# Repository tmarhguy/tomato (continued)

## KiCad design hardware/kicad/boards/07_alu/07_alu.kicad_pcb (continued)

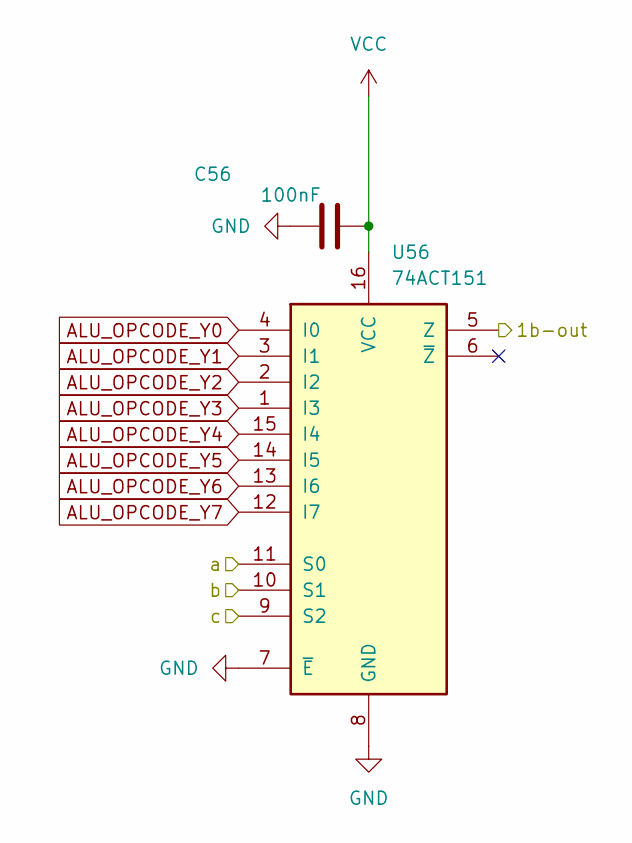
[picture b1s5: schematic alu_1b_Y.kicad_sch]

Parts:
C56: 100nF; C_0603_1608Metric
U56: 74ACT151; SOIC-16_3.9x9.9mm_P1.27mm

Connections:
/alu_4b_1/logB1: U56.5 (Z); also elsewhere on the board
A5: U56.11 (S0); also elsewhere on the board
ALU_OPCODE_Y0: U56.4 (I0); also elsewhere on the board
ALU_OPCODE_Y1: U56.3 (I1); also elsewhere on the board
ALU_OPCODE_Y2: U56.2 (I2); also elsewhere on the board
ALU_OPCODE_Y3: U56.1 (I3); also elsewhere on the board
ALU_OPCODE_Y4: U56.15 (I4); also elsewhere on the board
ALU_OPCODE_Y5: U56.14 (I5); also elsewhere on the board
ALU_OPCODE_Y6: U56.13 (I6); also elsewhere on the board
ALU_OPCODE_Y7: U56.12 (I7); also elsewhere on the board
B5: U56.10 (S1); also elsewhere on the board
C5: U56.9 (S2); also elsewhere on the board
GND: C56.1, U56.7 (~E), U56.8 (GND); also elsewhere on the board
VCC: C56.2, U56.16 (VCC); also elsewhere on the board

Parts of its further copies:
C41, C42, C43, C44, C55, C57, C58: 100nF; C_0603_1608Metric
U41, U42, U43, U44, U53, U54, U55: 74ACT151; SOIC-16_3.9x9.9mm_P1.27mm

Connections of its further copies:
/alu_4b_0/logB0: U41.5 (Z); also elsewhere on the board
/alu_4b_0/logB1: U42.5 (Z); also elsewhere on the board
/alu_4b_0/logB2: U43.5 (Z); also elsewhere on the board
/alu_4b_0/logB3: U44.5 (Z); also elsewhere on the board
/alu_4b_1/logB0: U53.5 (Z); also elsewhere on the board
/alu_4b_1/logB2: U54.5 (Z); also elsewhere on the board
A0: U41.11 (S0); also elsewhere on the board
A1: U42.11 (S0); also elsewhere on the board
A2: U43.11 (S0); also elsewhere on the board
A3: U44.11 (S0); also elsewhere on the board
A4: U53.11 (S0); also elsewhere on the board
A6: U54.11 (S0); also elsewhere on the board
A7: U55.11 (S0); also elsewhere on the board
ALU_OPCODE_Y0: U41.4 (I0), U42.4 (I0), U43.4 (I0), U44.4 (I0), U53.4 (I0), U54.4 (I0), U55.4 (I0); also elsewhere on the board
ALU_OPCODE_Y1: U41.3 (I1), U42.3 (I1), U43.3 (I1), U44.3 (I1), U53.3 (I1), U54.3 (I1), U55.3 (I1); also elsewhere on the board
ALU_OPCODE_Y2: U41.2 (I2), U42.2 (I2), U43.2 (I2), U44.2 (I2), U53.2 (I2), U54.2 (I2), U55.2 (I2); also elsewhere on the board
ALU_OPCODE_Y3: U41.1 (I3), U42.1 (I3), U43.1 (I3), U44.1 (I3), U53.1 (I3), U54.1 (I3), U55.1 (I3); also elsewhere on the board
ALU_OPCODE_Y4: U41.15 (I4), U42.15 (I4), U43.15 (I4), U44.15 (I4), U53.15 (I4), U54.15 (I4), U55.15 (I4); also elsewhere on the board
ALU_OPCODE_Y5: U41.14 (I5), U42.14 (I5), U43.14 (I5), U44.14 (I5), U53.14 (I5), U54.14 (I5), U55.14 (I5); also elsewhere on the board
ALU_OPCODE_Y6: U41.13 (I6), U42.13 (I6), U43.13 (I6), U44.13 (I6), U53.13 (I6), U54.13 (I6), U55.13 (I6); also elsewhere on the board
ALU_OPCODE_Y7: U41.12 (I7), U42.12 (I7), U43.12 (I7), U44.12 (I7), U53.12 (I7), U54.12 (I7), U55.12 (I7); also elsewhere on the board
B0: U41.10 (S1); also elsewhere on the board
B1: U42.10 (S1); also elsewhere on the board
B2: U43.10 (S1); also elsewhere on the board
B3: U44.10 (S1); also elsewhere on the board
B4: U53.10 (S1); also elsewhere on the board
B6: U54.10 (S1); also elsewhere on the board
B7: U55.10 (S1); also elsewhere on the board
Beff: U55.5 (Z); also elsewhere on the board
C0: U41.9 (S2); also elsewhere on the board
C1: U42.9 (S2); also elsewhere on the board
C2: U43.9 (S2); also elsewhere on the board
C3: U44.9 (S2); also elsewhere on the board
C4: U53.9 (S2); also elsewhere on the board
C6: U54.9 (S2); also elsewhere on the board
C7: U55.9 (S2); also elsewhere on the board
GND: C41.1, C42.1, C43.1, C44.1, C55.1, C57.1, C58.1, U41.7 (~E), U41.8 (GND), U42.7 (~E), U42.8 (GND), U43.7 (~E), U43.8 (GND), U44.7 (~E), U44.8 (GND), U53.7 (~E), U53.8 (GND), U54.7 (~E), U54.8 (GND), U55.7 (~E), U55.8 (GND); also elsewhere on the board
VCC: C41.2, C42.2, C43.2, C44.2, C55.2, C57.2, C58.2, U41.16 (VCC), U42.16 (VCC), U43.16 (VCC), U44.16 (VCC), U53.16 (VCC), U54.16 (VCC), U55.16 (VCC); also elsewhere on the board

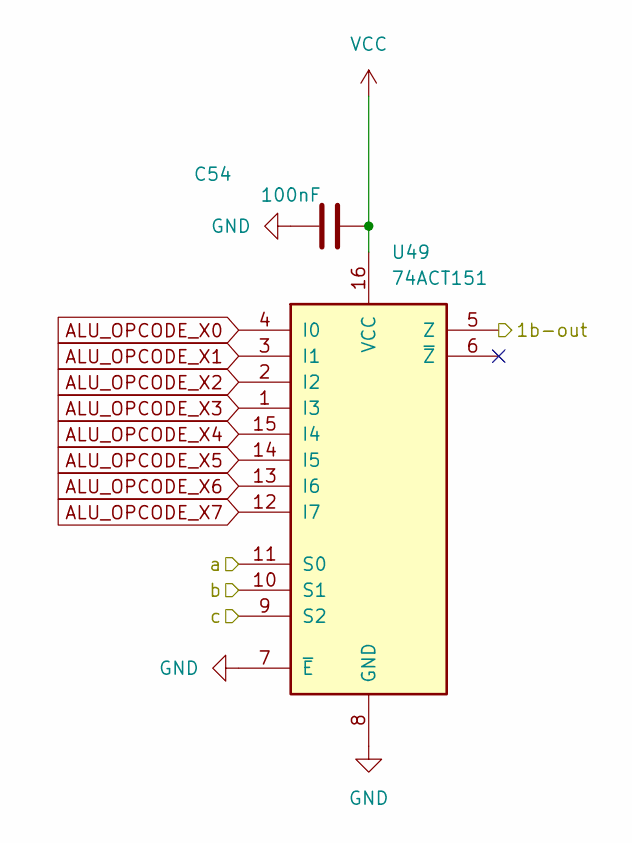
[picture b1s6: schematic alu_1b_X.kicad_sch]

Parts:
C54: 100nF; C_0603_1608Metric
U49: 74ACT151; SOIC-16_3.9x9.9mm_P1.27mm

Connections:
A7: U49.11 (S0); also elsewhere on the board
ALU_OPCODE_X0: U49.4 (I0); also elsewhere on the board
ALU_OPCODE_X1: U49.3 (I1); also elsewhere on the board
ALU_OPCODE_X2: U49.2 (I2); also elsewhere on the board
ALU_OPCODE_X3: U49.1 (I3); also elsewhere on the board
ALU_OPCODE_X4: U49.15 (I4); also elsewhere on the board
ALU_OPCODE_X5: U49.14 (I5); also elsewhere on the board
ALU_OPCODE_X6: U49.13 (I6); also elsewhere on the board
ALU_OPCODE_X7: U49.12 (I7); also elsewhere on the board
Aeff: U49.5 (Z); also elsewhere on the board
B7: U49.10 (S1); also elsewhere on the board
C7: U49.9 (S2); also elsewhere on the board
GND: C54.1, U49.7 (~E), U49.8 (GND); also elsewhere on the board
VCC: C54.2, U49.16 (VCC); also elsewhere on the board

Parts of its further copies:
C45, C46, C47, C48, C51, C52, C53: 100nF; C_0603_1608Metric
U45, U46, U47, U48, U50, U51, U52: 74ACT151; SOIC-16_3.9x9.9mm_P1.27mm

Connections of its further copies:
/alu_4b_0/logA0: U45.5 (Z); also elsewhere on the board
/alu_4b_0/logA1: U46.5 (Z); also elsewhere on the board
/alu_4b_0/logA2: U47.5 (Z); also elsewhere on the board
/alu_4b_0/logA3: U48.5 (Z); also elsewhere on the board
/alu_4b_1/logA0: U50.5 (Z); also elsewhere on the board
/alu_4b_1/logA1: U51.5 (Z); also elsewhere on the board
/alu_4b_1/logA2: U52.5 (Z); also elsewhere on the board
A0: U45.11 (S0); also elsewhere on the board
A1: U46.11 (S0); also elsewhere on the board
A2: U47.11 (S0); also elsewhere on the board
A3: U48.11 (S0); also elsewhere on the board
A4: U50.11 (S0); also elsewhere on the board
A5: U51.11 (S0); also elsewhere on the board
A6: U52.11 (S0); also elsewhere on the board
ALU_OPCODE_X0: U45.4 (I0), U46.4 (I0), U47.4 (I0), U48.4 (I0), U50.4 (I0), U51.4 (I0), U52.4 (I0); also elsewhere on the board
ALU_OPCODE_X1: U45.3 (I1), U46.3 (I1), U47.3 (I1), U48.3 (I1), U50.3 (I1), U51.3 (I1), U52.3 (I1); also elsewhere on the board
ALU_OPCODE_X2: U45.2 (I2), U46.2 (I2), U47.2 (I2), U48.2 (I2), U50.2 (I2), U51.2 (I2), U52.2 (I2); also elsewhere on the board
ALU_OPCODE_X3: U45.1 (I3), U46.1 (I3), U47.1 (I3), U48.1 (I3), U50.1 (I3), U51.1 (I3), U52.1 (I3); also elsewhere on the board
ALU_OPCODE_X4: U45.15 (I4), U46.15 (I4), U47.15 (I4), U48.15 (I4), U50.15 (I4), U51.15 (I4), U52.15 (I4); also elsewhere on the board
ALU_OPCODE_X5: U45.14 (I5), U46.14 (I5), U47.14 (I5), U48.14 (I5), U50.14 (I5), U51.14 (I5), U52.14 (I5); also elsewhere on the board
ALU_OPCODE_X6: U45.13 (I6), U46.13 (I6), U47.13 (I6), U48.13 (I6), U50.13 (I6), U51.13 (I6), U52.13 (I6); also elsewhere on the board
ALU_OPCODE_X7: U45.12 (I7), U46.12 (I7), U47.12 (I7), U48.12 (I7), U50.12 (I7), U51.12 (I7), U52.12 (I7); also elsewhere on the board
B0: U45.10 (S1); also elsewhere on the board
B1: U46.10 (S1); also elsewhere on the board
B2: U47.10 (S1); also elsewhere on the board
B3: U48.10 (S1); also elsewhere on the board
B4: U50.10 (S1); also elsewhere on the board
B5: U51.10 (S1); also elsewhere on the board
B6: U52.10 (S1); also elsewhere on the board
C0: U45.9 (S2); also elsewhere on the board
C1: U46.9 (S2); also elsewhere on the board
C2: U47.9 (S2); also elsewhere on the board
C3: U48.9 (S2); also elsewhere on the board
C4: U50.9 (S2); also elsewhere on the board
C5: U51.9 (S2); also elsewhere on the board
C6: U52.9 (S2); also elsewhere on the board
GND: C45.1, C46.1, C47.1, C48.1, C51.1, C52.1, C53.1, U45.7 (~E), U45.8 (GND), U46.7 (~E), U46.8 (GND), U47.7 (~E), U47.8 (GND), U48.7 (~E), U48.8 (GND), U50.7 (~E), U50.8 (GND), U51.7 (~E), U51.8 (GND), U52.7 (~E), U52.8 (GND); also elsewhere on the board
VCC: C45.2, C46.2, C47.2, C48.2, C51.2, C52.2, C53.2, U45.16 (VCC), U46.16 (VCC), U47.16 (VCC), U48.16 (VCC), U50.16 (VCC), U51.16 (VCC), U52.16 (VCC); also elsewhere on the board

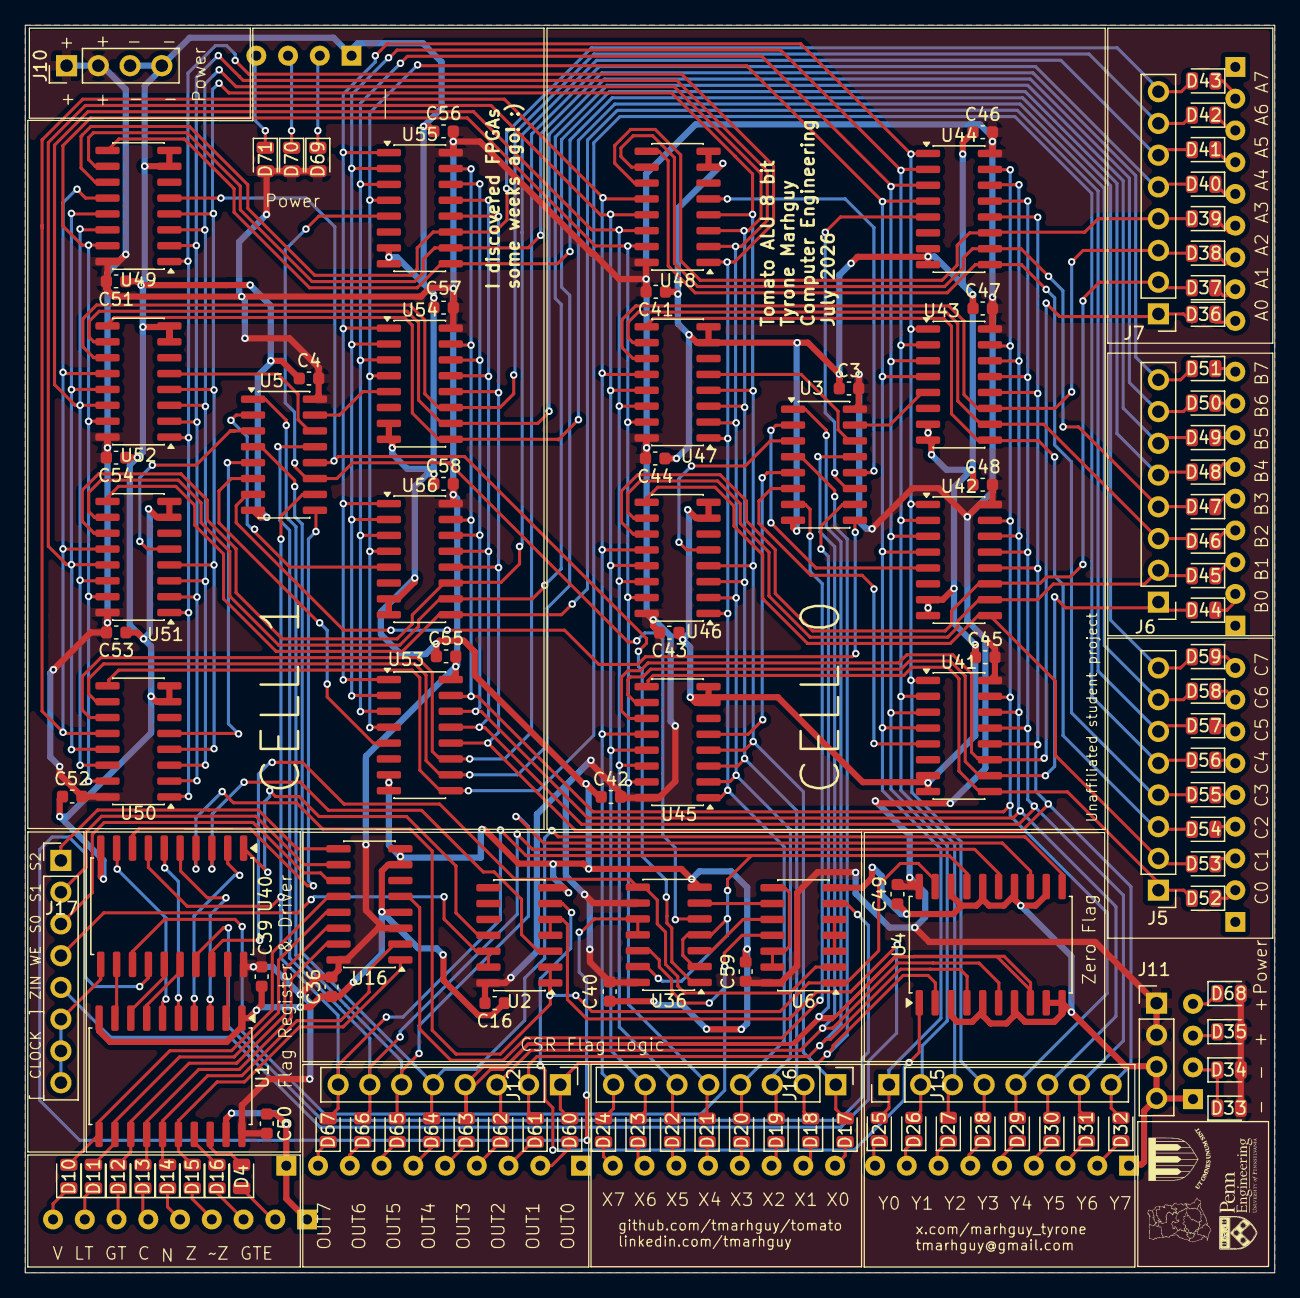
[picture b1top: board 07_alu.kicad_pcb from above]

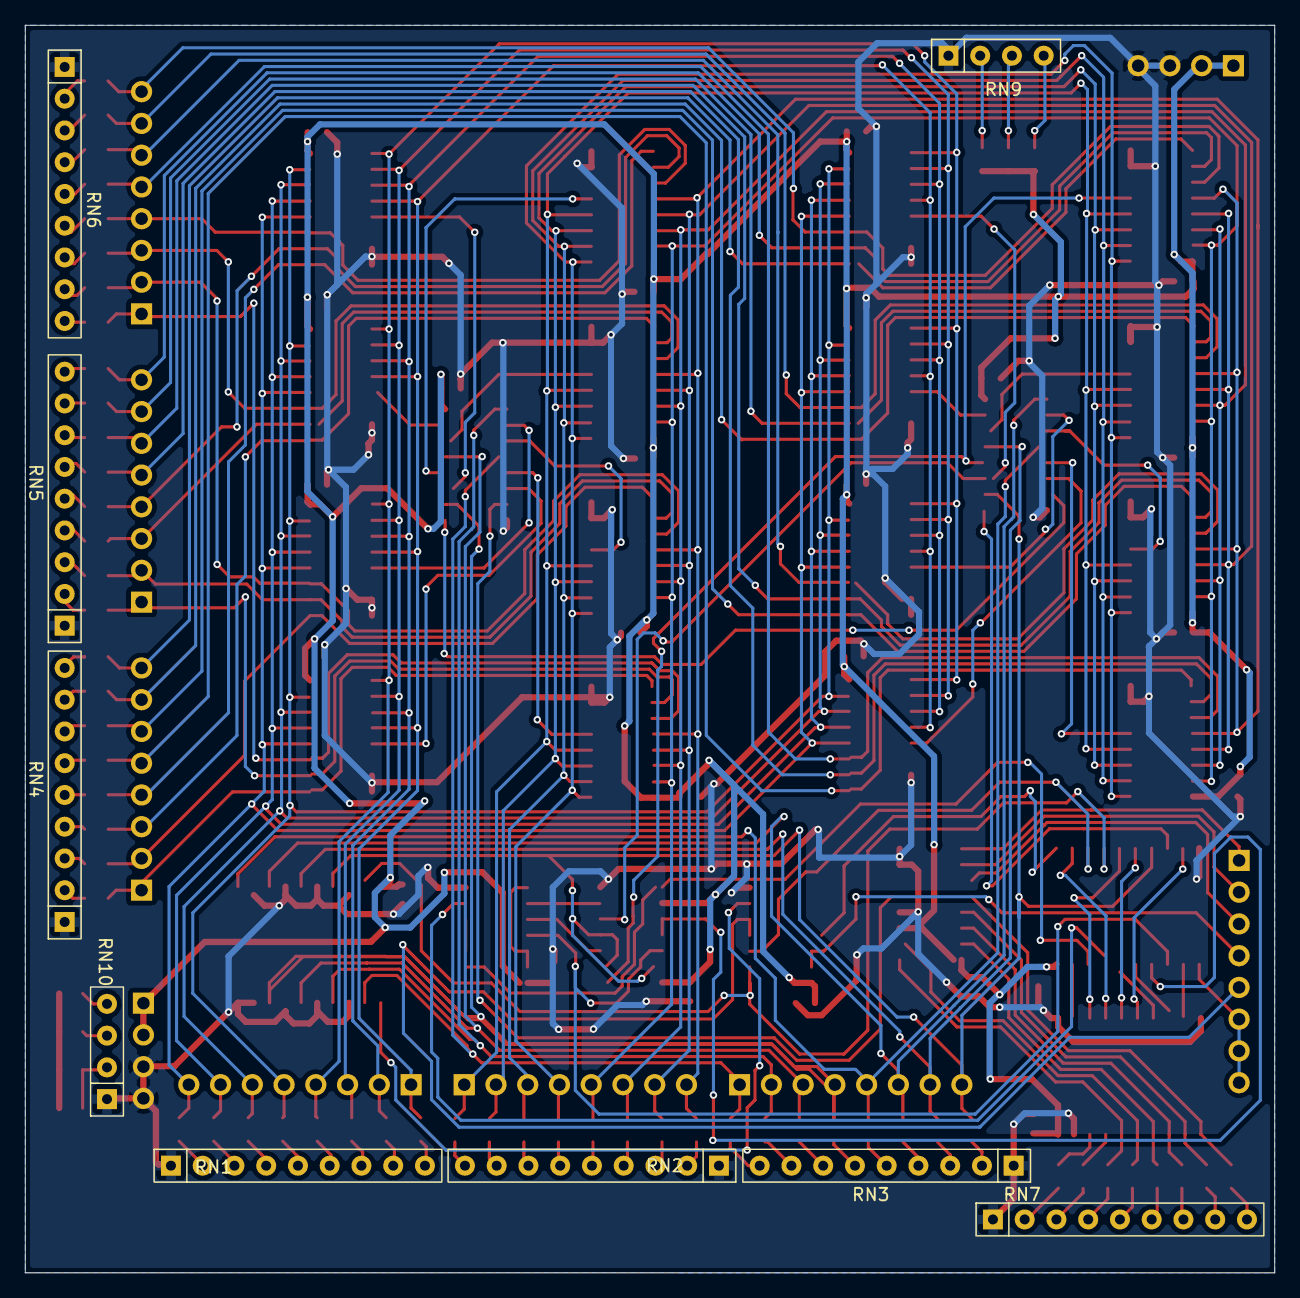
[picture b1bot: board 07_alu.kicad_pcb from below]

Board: 2 copper layers, 100.0 x 99.8 mm, 134 parts (9 on the bottom side), 165 nets.

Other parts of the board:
Ref**: Val**; ghana_map
Ref**#2: Val**; upenn_eng_logo
Ref**#3: Val**; achimota_logo

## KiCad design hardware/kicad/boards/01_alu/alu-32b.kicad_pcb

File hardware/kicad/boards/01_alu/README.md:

# 01 — Early ALU (historical)

<p align="center"><strong>Pre-Tomato experiments · superseded by Lot 07.</strong></p>

Archive lot for early ALU board work. The living Dual-LUT PCB is **[07_alu](../07_alu/README.md)**. The prior 8-bit discrete-transistor story (270×270 mm, ~3,488 devices) is documented at [alu.tmarhguy.com](https://alu.tmarhguy.com).

**Project map:** [Boards](../README.md) · [07_alu](../07_alu/README.md) · [Root README](../../../../README.md)

---

# Legacy notes (transistor-era board)

**Monolithic 8-bit ALU — complete combinational processor on a single PCB** (historical reference below).

## Specifications

| Parameter | Value |
|-----------|-------|
| **Board Size** | 270mm × 270mm (10.6" × 10.6") = **72900 mm²** |
| **Transistor Count** | 3,488 (Hybrid: Discrete + equivalent ICs) → **436 T/bit** |
| **Board mm² / bit** | **≈9112** (72900 / 8) |
| **Architecture** | Pure combinational (no clock) |
| **Layers** | 2 (top signal/power, bottom ground) |
| **Power** | 5V @ 0.5-1A (idle bring-up **&lt;200 mA**) |
| **Propagation Delay** | ~445ns (worst case) |

---

## Functional Blocks

### Arithmetic Unit (Top-Left Quadrant)

**Components:**
- 8× 1-bit full adders (336T)
- 8× XOR gates for B input (96T)
- Carry chain routing

**Function:** A + B or A - B (via 2's complement)

**Signals:**
```
IN:  A[7:0], B[7:0], M
OUT: SUM[7:0], COUT
```

### Logic Unit (Top-Right Quadrant)

**Components:**
- NAND array (32T)
- NOR array (32T)
- XOR array (96T)
- PASS A/B buffers (32T)
- 5:1 MUX (160T)

**Function:** NAND, NOR, XOR, PASS A, PASS B operations

**Signals:**
```
IN:  A[7:0], B[7:0], LOGIC_SEL[2:0]
OUT: LOGIC_OUT[7:0]
```

### Selection & Output (Center)

**Components:**
- 2:1 MUX (160T) - arithmetic vs logic select
- Global inverter (16T)

**Function:** Select result and optionally invert

**Signals:**
```
IN:  ARITH[7:0], LOGIC[7:0], MUX_SEL, INV_OUT
OUT: RESULT[7:0]
```

### Flag Generation (Bottom-Left Quadrant)

**Components:**
- EQUAL comparator (~100T)
- LESS comparator (~120T)
- POSITIVE detector (~20T)

**Function:** Generate comparison and status flags

**Signals:**
```
IN:  A[7:0], B[7:0], OUT[7:0], COUT_IN
OUT: LESS, EQUAL, POSITIVE, COUT
```

### Control Decoder (Bottom-Right Quadrant)

**Components:**
- Combinational decode logic (~68T)

**Function:** FUNC[4:0] → control signals

**Signals:**
```
IN:  FUNC[4:0]
OUT: M, MUX_SEL, INV_OUT, LOGIC_SEL[2:0]
```

---

## Pinout

### Input Pins (22 total)

| Pin Group | Count | Description |
|-----------|-------|-------------|
| A[7:0] | 8 | First operand |
| B[7:0] | 8 | Second operand |
| FUNC[4:0] | 5 | Opcode |
| VCC | 1 | +5V power |
| GND | 1 | Ground (multiple connections) |

### Output Pins (12 total)

| Pin Group | Count | Description |
|-----------|-------|-------------|
| OUT[7:0] | 8 | Result |
| LESS | 1 | Less than flag |
| EQUAL | 1 | Equal flag |
| POSITIVE | 1 | Positive flag |
| COUT | 1 | Carry out flag |

---

## Fabrication

### Manufacturing Requirements

**PCB Specs:**
- **Size:** 270×270mm (**confirm manufacturer supports large format**)
- **Layers:** 2
- **Thickness:** 1.6mm
- **Copper:** 1oz (35µm)
- **Min trace/space:** 0.2mm/0.2mm
- **Surface finish:** HASL lead-free

### Assembly

**Component count:**
- 3,488 transistors (624 Discrete + 2,864 in ICs + Support)
- ~500 resistors (10kΩ pull-ups, 220Ω current limiting)
- ~50 capacitors (100nF decoupling)
- 36x 74HC157 + 10x 74HC86 ICs
- Headers, test points

**Estimated assembly time:** 50-70 hours (hand soldering)

---

## Testing

### Power-On Test

```
1. Visual inspection
2. Continuity: VCC, GND
3. Resistance: VCC-GND > 10kΩ
4. Power-on: Measure current < 200mA idle
5. Voltage: VCC = 5.0V ± 0.1V at all points
```

### Functional Test

```
Test ADD operation:
  FUNC = 00000
  A = 0x01
  B = 0x01
  Expected OUT = 0x02
  Measure with multimeter or logic analyzer
```

---

## References

- [Schematic](main_alu.kicad_sch) - Complete circuit
- [PCB Layout](main_alu.kicad_pcb) - Board layout
- [Architecture](../../../docs/ARCHITECTURE.md) - System design

---

**Status:** Design complete, fabrication-ready  
**Last Updated:** 2026-01-16

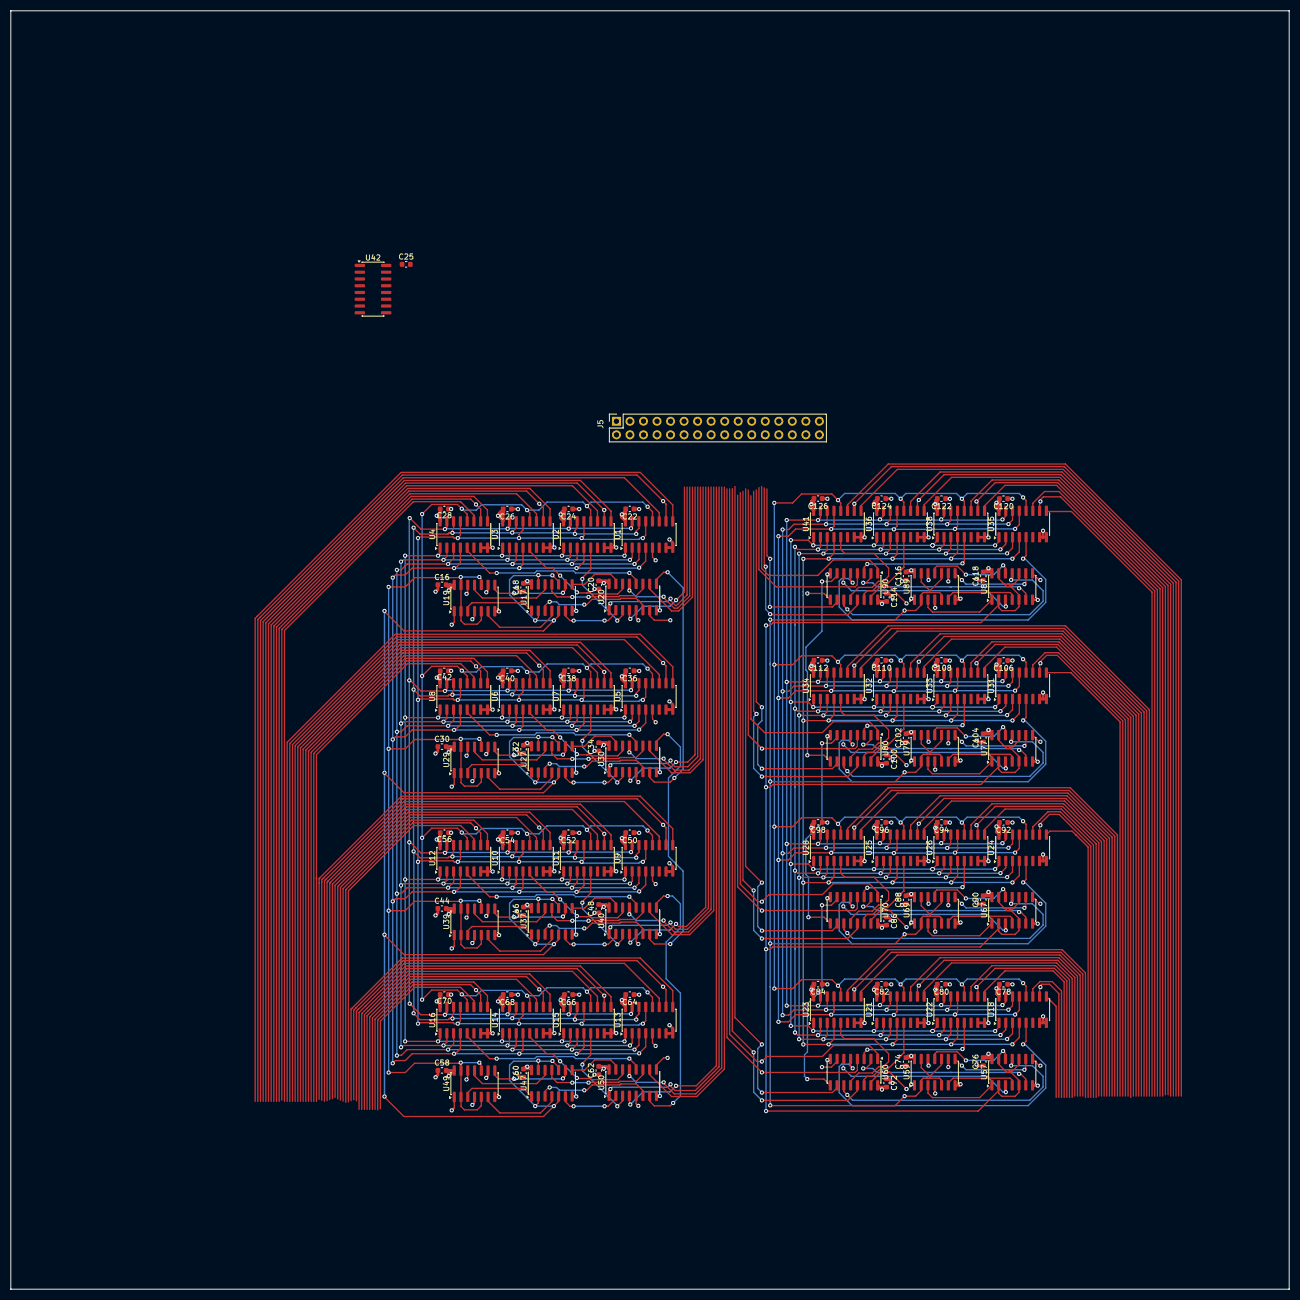
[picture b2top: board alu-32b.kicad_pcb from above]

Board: 4 copper layers, 240.0 x 240.0 mm, 115 parts (0 on the bottom side), 179 nets.

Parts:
C16, C18, C20, C22, C24, C25, C26, C28, C30, C32, C34, C36, C38, C40, C42, C44, C46, C48, C50, C52, C54, C56, C58, C60, C62, C64, C66, C68, C70, C72, C74, C76, C78, C80, C82, C84, C86, C88, C90, C92, C94, C96, C98, C100, C102, C104, C106, C108, C110, C112, C114, C116, C118, C120, C122, C124, C126: 100nF; C_0603_1608Metric
J5: Conn_02x16_Counter_Clockwise; PinSocket_2x16_P2.54mm_Vertical
U1, U2, U3, U4, U5, U6, U7, U8, U9, U10, U11, U12, U13, U14, U15, U16, U18, U21, U22, U23, U24, U25, U26, U28, U31, U32, U33, U34, U35, U36, U38, U41, U42: 74ACT151; SOIC-16_3.9x9.9mm_P1.27mm
U17, U27, U37, U47, U57, U67, U77, U87: 74HC86; SOIC-14_3.9x8.7mm_P1.27mm
U19, U29, U39, U49, U59, U69, U79, U89: 74HC00; SOIC-14_3.9x8.7mm_P1.27mm
U20, U30, U40, U50, U60, U70, U80, U90: 74ACT283; SOIC-16_3.9x9.9mm_P1.27mm

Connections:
/alu-4b-0/log0: U1.5 (Z), U20.5 (A1)
/alu-4b-0/log1: U2.5 (Z), U20.3 (A2)
/alu-4b-0/log2: U3.5 (Z), U20.14 (A3)
/alu-4b-0/log3: U4.5 (Z), U20.12 (A4)
/alu-4b-0/sB0: U17.3, U20.6 (B1)
/alu-4b-0/sB1: U17.6, U20.2 (B2)
/alu-4b-0/sB2: U17.8, U20.15 (B3)
/alu-4b-0/sB3: U17.11, U20.11 (B4)
/alu-4b-1/log0: U5.5 (Z), U30.5 (A1)
/alu-4b-1/log1: U7.5 (Z), U30.3 (A2)
/alu-4b-1/log2: U6.5 (Z), U30.14 (A3)
/alu-4b-1/log3: U8.5 (Z), U30.12 (A4)
/alu-4b-1/sB0: U27.3, U30.6 (B1)
/alu-4b-1/sB1: U27.6, U30.2 (B2)
/alu-4b-1/sB2: U27.8, U30.15 (B3)
/alu-4b-1/sB3: U27.11, U30.11 (B4)
/alu-4b-2/log0: U9.5 (Z), U40.5 (A1)
/alu-4b-2/log1: U11.5 (Z), U40.3 (A2)
/alu-4b-2/log2: U10.5 (Z), U40.14 (A3)
/alu-4b-2/log3: U12.5 (Z), U40.12 (A4)
/alu-4b-2/sB0: U37.3, U40.6 (B1)
/alu-4b-2/sB1: U37.6, U40.2 (B2)
/alu-4b-2/sB2: U37.8, U40.15 (B3)
/alu-4b-2/sB3: U37.11, U40.11 (B4)
/alu-4b-3/log0: U13.5 (Z), U50.5 (A1)
/alu-4b-3/log1: U15.5 (Z), U50.3 (A2)
/alu-4b-3/log2: U14.5 (Z), U50.14 (A3)
/alu-4b-3/log3: U16.5 (Z), U50.12 (A4)
/alu-4b-3/sB0: U47.3, U50.6 (B1)
/alu-4b-3/sB1: U47.6, U50.2 (B2)
/alu-4b-3/sB2: U47.8, U50.15 (B3)
/alu-4b-3/sB3: U47.11, U50.11 (B4)
/alu-4b-4/log0: U18.5 (Z), U60.5 (A1)
/alu-4b-4/log1: U22.5 (Z), U60.3 (A2)
/alu-4b-4/log2: U21.5 (Z), U60.14 (A3)
/alu-4b-4/log3: U23.5 (Z), U60.12 (A4)
/alu-4b-4/sB0: U57.3, U60.6 (B1)
/alu-4b-4/sB1: U57.6, U60.2 (B2)
/alu-4b-4/sB2: U57.8, U60.15 (B3)
/alu-4b-4/sB3: U57.11, U60.11 (B4)
/alu-4b-5/log0: U24.5 (Z), U70.5 (A1)
/alu-4b-5/log1: U26.5 (Z), U70.3 (A2)
/alu-4b-5/log2: U25.5 (Z), U70.14 (A3)
/alu-4b-5/log3: U28.5 (Z), U70.12 (A4)
/alu-4b-5/sB0: U67.3, U70.6 (B1)
/alu-4b-5/sB1: U67.6, U70.2 (B2)
/alu-4b-5/sB2: U67.8, U70.15 (B3)
/alu-4b-5/sB3: U67.11, U70.11 (B4)
/alu-4b-6/log0: U31.5 (Z), U80.5 (A1)
/alu-4b-6/log1: U33.5 (Z), U80.3 (A2)
/alu-4b-6/log2: U32.5 (Z), U80.14 (A3)
/alu-4b-6/log3: U34.5 (Z), U80.12 (A4)
/alu-4b-6/sB0: U77.3, U80.6 (B1)
/alu-4b-6/sB1: U77.6, U80.2 (B2)
/alu-4b-6/sB2: U77.8, U80.15 (B3)
/alu-4b-6/sB3: U77.11, U80.11 (B4)
/alu-4b-7/log0: U35.5 (Z), U90.5 (A1)
/alu-4b-7/log1: U38.5 (Z), U90.3 (A2)
/alu-4b-7/log2: U36.5 (Z), U90.14 (A3)
/alu-4b-7/sB0: U87.3, U90.6 (B1)
/alu-4b-7/sB1: U87.6, U90.2 (B2)
/alu-4b-7/sB2: U87.8, U90.15 (B3)
/cout0: U20.9 (C4), U30.7 (C0)
/cout1: U30.9 (C4), U40.7 (C0)
/cout2: U40.9 (C4), U50.7 (C0)
/cout3: U50.9 (C4), U60.7 (C0)
/cout4: U60.9 (C4), U70.7 (C0)
/cout5: U70.9 (C4), U80.7 (C0)
/cout6: U80.9 (C4), U90.7 (C0)
AEFF31: U41.5 (Z), U90.12 (A4)
ALU-OPCODE0: U1.4 (I0), U2.4 (I0), U3.4 (I0), U4.4 (I0), U5.4 (I0), U6.4 (I0), U7.4 (I0), U8.4 (I0), U9.4 (I0), U10.4 (I0), U11.4 (I0), U12.4 (I0), U13.4 (I0), U14.4 (I0), U15.4 (I0), U16.4 (I0), U18.4 (I0), U21.4 (I0), U22.4 (I0), U23.4 (I0), U24.4 (I0), U25.4 (I0), U26.4 (I0), U28.4 (I0), U31.4 (I0), U32.4 (I0), U33.4 (I0), U34.4 (I0), U35.4 (I0), U36.4 (I0), U38.4 (I0), U41.4 (I0)
ALU-OPCODE1: U1.3 (I1), U2.3 (I1), U3.3 (I1), U4.3 (I1), U5.3 (I1), U6.3 (I1), U7.3 (I1), U8.3 (I1), U9.3 (I1), U10.3 (I1), U11.3 (I1), U12.3 (I1), U13.3 (I1), U14.3 (I1), U15.3 (I1), U16.3 (I1), U18.3 (I1), U21.3 (I1), U22.3 (I1), U23.3 (I1), U24.3 (I1), U25.3 (I1), U26.3 (I1), U28.3 (I1), U31.3 (I1), U32.3 (I1), U33.3 (I1), U34.3 (I1), U35.3 (I1), U36.3 (I1), U38.3 (I1), U41.3 (I1)
ALU-OPCODE2: U1.2 (I2), U2.2 (I2), U3.2 (I2), U4.2 (I2), U5.2 (I2), U6.2 (I2), U7.2 (I2), U8.2 (I2), U9.2 (I2), U10.2 (I2), U11.2 (I2), U12.2 (I2), U13.2 (I2), U14.2 (I2), U15.2 (I2), U16.2 (I2), U18.2 (I2), U21.2 (I2), U22.2 (I2), U23.2 (I2), U24.2 (I2), U25.2 (I2), U26.2 (I2), U28.2 (I2), U31.2 (I2), U32.2 (I2), U33.2 (I2), U34.2 (I2), U35.2 (I2), U36.2 (I2), U38.2 (I2), U41.2 (I2)
ALU-OPCODE3: U1.1 (I3), U2.1 (I3), U3.1 (I3), U4.1 (I3), U5.1 (I3), U6.1 (I3), U7.1 (I3), U8.1 (I3), U9.1 (I3), U10.1 (I3), U11.1 (I3), U12.1 (I3), U13.1 (I3), U14.1 (I3), U15.1 (I3), U16.1 (I3), U18.1 (I3), U21.1 (I3), U22.1 (I3), U23.1 (I3), U24.1 (I3), U25.1 (I3), U26.1 (I3), U28.1 (I3), U31.1 (I3), U32.1 (I3), U33.1 (I3), U34.1 (I3), U35.1 (I3), U36.1 (I3), U38.1 (I3), U41.1 (I3)
ALU-OPCODE4: U1.15 (I4), U2.15 (I4), U3.15 (I4), U4.15 (I4), U5.15 (I4), U6.15 (I4), U7.15 (I4), U8.15 (I4), U9.15 (I4), U10.15 (I4), U11.15 (I4), U12.15 (I4), U13.15 (I4), U14.15 (I4), U15.15 (I4), U16.15 (I4), U18.15 (I4), U21.15 (I4), U22.15 (I4), U23.15 (I4), U24.15 (I4), U25.15 (I4), U26.15 (I4), U28.15 (I4), U31.15 (I4), U32.15 (I4), U33.15 (I4), U34.15 (I4), U35.15 (I4), U36.15 (I4), U38.15 (I4), U41.15 (I4)
ALU-OPCODE5: U1.14 (I5), U2.14 (I5), U3.14 (I5), U4.14 (I5), U5.14 (I5), U6.14 (I5), U7.14 (I5), U8.14 (I5), U9.14 (I5), U10.14 (I5), U11.14 (I5), U12.14 (I5), U13.14 (I5), U14.14 (I5), U15.14 (I5), U16.14 (I5), U18.14 (I5), U21.14 (I5), U22.14 (I5), U23.14 (I5), U24.14 (I5), U25.14 (I5), U26.14 (I5), U28.14 (I5), U31.14 (I5), U32.14 (I5), U33.14 (I5), U34.14 (I5), U35.14 (I5), U36.14 (I5), U38.14 (I5), U41.14 (I5)
ALU-OPCODE6: U1.13 (I6), U2.13 (I6), U3.13 (I6), U4.13 (I6), U5.13 (I6), U6.13 (I6), U7.13 (I6), U8.13 (I6), U9.13 (I6), U10.13 (I6), U11.13 (I6), U12.13 (I6), U13.13 (I6), U14.13 (I6), U15.13 (I6), U16.13 (I6), U18.13 (I6), U21.13 (I6), U22.13 (I6), U23.13 (I6), U24.13 (I6), U25.13 (I6), U26.13 (I6), U28.13 (I6), U31.13 (I6), U32.13 (I6), U33.13 (I6), U34.13 (I6), U35.13 (I6), U36.13 (I6), U38.13 (I6), U41.13 (I6)
ALU-OPCODE7: U1.12 (I7), U2.12 (I7), U3.12 (I7), U4.12 (I7), U5.12 (I7), U6.12 (I7), U7.12 (I7), U8.12 (I7), U9.12 (I7), U10.12 (I7), U11.12 (I7), U12.12 (I7), U13.12 (I7), U14.12 (I7), U15.12 (I7), U16.12 (I7), U18.12 (I7), U21.12 (I7), U22.12 (I7), U23.12 (I7), U24.12 (I7), U25.12 (I7), U26.12 (I7), U28.12 (I7), U31.12 (I7), U32.12 (I7), U33.12 (I7), U34.12 (I7), U35.12 (I7), U36.12 (I7), U38.12 (I7), U41.12 (I7)
B0: U1.10 (S1), U19.1
B1: U2.10 (S1), U19.4
B2: U3.10 (S1), U19.9
B3: U4.10 (S1), U19.12
B4: U5.10 (S1), U29.1
B5: U7.10 (S1), U29.4
B6: U6.10 (S1), U29.9
B7: U8.10 (S1), U29.12
B8: U9.10 (S1), U39.1
B9: U11.10 (S1), U39.4
B10: U10.10 (S1), U39.9
B11: U12.10 (S1), U39.12
B12: U13.10 (S1), U49.1
B13: U15.10 (S1), U49.4
B14: U14.10 (S1), U49.9
B15: U16.10 (S1), U49.12
B16: U18.10 (S1), U59.1
B17: U22.10 (S1), U59.4
B18: U21.10 (S1), U59.9
B19: U23.10 (S1), U59.12
B20: U24.10 (S1), U69.1
B21: U26.10 (S1), U69.4
B22: U25.10 (S1), U69.9
B23: U28.10 (S1), U69.12
B24: U31.10 (S1), U79.1
B25: U33.10 (S1), U79.4
B26: U32.10 (S1), U79.9
B27: U34.10 (S1), U79.12
B28: U35.10 (S1), U89.1
B29: U38.10 (S1), U89.4
B30: U36.10 (S1), U89.9
B31: U41.10 (S1), U89.12
BEFF31: U87.11, U90.11 (B4)
GND: C16.1, C18.1, C20.1, C22.1, C24.1, C25.1, C26.1, C28.1, C30.1, C32.1, C34.1, C36.1, C38.1, C40.1, C42.1, C44.1, C46.1, C48.1, C50.1, C52.1, C54.1, C56.1, C58.1, C60.1, C62.1, C64.1, C66.1, C68.1, C70.1, C72.1, C74.1, C76.1, C78.1, C80.1, C82.1, C84.1, C86.1, C88.1, C90.1, C92.1, C94.1, C96.1, C98.1, C100.1, C102.1, C104.1, C106.1, C108.1, C110.1, C112.1, C114.1, C116.1, C118.1, C120.1, C122.1, C124.1, C126.1, U1.7 (~E), U1.8 (GND), U2.7 (~E), U2.8 (GND), U3.7 (~E), U3.8 (GND), U4.7 (~E), U4.8 (GND), U5.7 (~E), U5.8 (GND), U6.7 (~E), U6.8 (GND), U7.7 (~E), U7.8 (GND), U8.7 (~E), U8.8 (GND), U9.7 (~E), U9.8 (GND), U10.7 (~E), U10.8 (GND), U11.7 (~E), U11.8 (GND), U12.7 (~E), U12.8 (GND), U13.7 (~E), U13.8 (GND), U14.7 (~E), U14.8 (GND), U15.7 (~E), U15.8 (GND), U16.7 (~E), U16.8 (GND), U17.7 (GND), U18.7 (~E), U18.8 (GND), U19.7 (GND), U20.8 (GND), U21.7 (~E), U21.8 (GND), U22.7 (~E), U22.8 (GND), U23.7 (~E), U23.8 (GND), U24.7 (~E), U24.8 (GND), U25.7 (~E), U25.8 (GND), U26.7 (~E), U26.8 (GND), U27.7 (GND), U28.7 (~E), U28.8 (GND), U29.7 (GND), U30.8 (GND), U31.7 (~E), U31.8 (GND), U32.7 (~E), U32.8 (GND), U33.7 (~E), U33.8 (GND), U34.7 (~E), U34.8 (GND), U35.7 (~E), U35.8 (GND), U36.7 (~E), U36.8 (GND), U37.7 (GND), U38.7 (~E), U38.8 (GND), U39.7 (GND), U40.8 (GND), U41.7 (~E), U41.8 (GND), U42.4 (I0), U42.7 (~E), U42.8 (GND), U47.7 (GND), U49.7 (GND), U50.8 (GND), U57.7 (GND), U59.7 (GND), U60.8 (GND), U67.7 (GND), U69.7 (GND), U70.8 (GND), U77.7 (GND), U79.7 (GND), U80.8 (GND), U87.7 (GND), U89.7 (GND), U90.8 (GND)
unnamed: U17.1, U19.3
unnamed: U17.4, U19.6
unnamed: U17.9, U19.8
unnamed: U17.12, U19.11
unnamed: U27.1, U29.3
unnamed: U27.4, U29.6
unnamed: U27.9, U29.8
unnamed: U27.12, U29.11
unnamed: U37.1, U39.3
unnamed: U37.4, U39.6
unnamed: U37.9, U39.8
unnamed: U37.12, U39.11
unnamed: U47.1, U49.3
unnamed: U47.4, U49.6
unnamed: U47.9, U49.8
unnamed: U47.12, U49.11
unnamed: U57.1, U59.3
unnamed: U57.4, U59.6
unnamed: U57.9, U59.8
unnamed: U57.12, U59.11
unnamed: U67.1, U69.3
unnamed: U67.4, U69.6
unnamed: U67.9, U69.8
unnamed: U67.12, U69.11
unnamed: U77.1, U79.3
unnamed: U77.4, U79.6
unnamed: U77.9, U79.8
unnamed: U77.12, U79.11
unnamed: U87.1, U89.3
unnamed: U87.4, U89.6
unnamed: U87.9, U89.8
unnamed: U87.12, U89.11
OUT0: J5.1, U20.4 (S1)
OUT1: J5.2, U20.1 (S2)
OUT2: J5.3, U20.13 (S3)
OUT3: J5.4, U20.10 (S4)
OUT4: J5.5, U30.4 (S1)
OUT5: J5.6, U30.1 (S2)
OUT6: J5.7, U30.13 (S3)
OUT7: J5.8, U30.10 (S4)
OUT8: J5.9, U40.4 (S1)
OUT9: J5.10, U40.1 (S2)
OUT10: J5.11, U40.13 (S3)
OUT11: J5.12, U40.10 (S4)
OUT12: J5.13, U50.4 (S1)
OUT13: J5.14, U50.1 (S2)
OUT14: J5.15, U50.13 (S3)
OUT15: J5.16, U50.10 (S4)
OUT16: J5.17, U60.4 (S1)
OUT17: J5.18, U60.1 (S2)
OUT18: J5.19, U60.13 (S3)
OUT19: J5.20, U60.10 (S4)
OUT20: J5.21, U70.4 (S1)
OUT21: J5.22, U70.1 (S2)
OUT22: J5.23, U70.13 (S3)
OUT23: J5.24, U70.10 (S4)
OUT24: J5.25, U80.4 (S1)
OUT25: J5.26, U80.1 (S2)
OUT26: J5.27, U80.13 (S3)
OUT27: J5.28, U80.10 (S4)
OUT28: J5.29, U90.4 (S1)
OUT29: J5.30, U90.1 (S2)
OUT30: J5.31, U90.13 (S3)
VCC: C16.2, C18.2, C20.2, C22.2, C24.2, C25.2, C26.2, C28.2, C30.2, C32.2, C34.2, C36.2, C38.2, C40.2, C42.2, C44.2, C46.2, C48.2, C50.2, C52.2, C54.2, C56.2, C58.2, C60.2, C62.2, C64.2, C66.2, C68.2, C70.2, C72.2, C74.2, C76.2, C78.2, C80.2, C82.2, C84.2, C86.2, C88.2, C90.2, C92.2, C94.2, C96.2, C98.2, C100.2, C102.2, C104.2, C106.2, C108.2, C110.2, C112.2, C114.2, C116.2, C118.2, C120.2, C122.2, C124.2, C126.2, U1.16 (VCC), U2.16 (VCC), U3.16 (VCC), U4.16 (VCC), U5.16 (VCC), U6.16 (VCC), U7.16 (VCC), U8.16 (VCC), U9.16 (VCC), U10.16 (VCC), U11.16 (VCC), U12.16 (VCC), U13.16 (VCC), U14.16 (VCC), U15.16 (VCC), U16.16 (VCC), U17.14 (VCC), U18.16 (VCC), U19.14 (VCC), U20.16 (VCC), U21.16 (VCC), U22.16 (VCC), U23.16 (VCC), U24.16 (VCC), U25.16 (VCC), U26.16 (VCC), U27.14 (VCC), U28.16 (VCC), U29.14 (VCC), U30.16 (VCC), U31.16 (VCC), U32.16 (VCC), U33.16 (VCC), U34.16 (VCC), U35.16 (VCC), U36.16 (VCC), U37.14 (VCC), U38.16 (VCC), U39.14 (VCC), U40.16 (VCC), U41.16 (VCC), U42.3 (I1), U42.16 (VCC), U47.14 (VCC), U49.14 (VCC), U50.16 (VCC), U57.14 (VCC), U59.14 (VCC), U60.16 (VCC), U67.14 (VCC), U69.14 (VCC), U70.16 (VCC), U77.14 (VCC), U79.14 (VCC), U80.16 (VCC), U87.14 (VCC), U89.14 (VCC), U90.16 (VCC)
binv: U17.2, U17.5, U17.10, U17.13, U27.2, U27.5, U27.10, U27.13, U37.2, U37.5, U37.10, U37.13, U47.2, U47.5, U47.10, U47.13, U57.2, U57.5, U57.10, U57.13, U67.2, U67.5, U67.10, U67.13, U77.2, U77.5, U77.10, U77.13, U87.2, U87.5, U87.10, U87.13
bsel: U19.2, U19.5, U19.10, U19.13, U29.2, U29.5, U29.10, U29.13, U39.2, U39.5, U39.10, U39.13, U49.2, U49.5, U49.10, U49.13, U59.2, U59.5, U59.10, U59.13, U69.2, U69.5, U69.10, U69.13, U79.2, U79.5, U79.10, U79.13, U89.2, U89.5, U89.10, U89.13
cin-main: U20.7 (C0), U42.5 (Z)

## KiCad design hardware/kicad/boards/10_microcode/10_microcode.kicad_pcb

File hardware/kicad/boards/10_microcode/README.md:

# 10_microcode

This board corresponds to the `10_microcode` module.
Add schematic and PCB design details here.

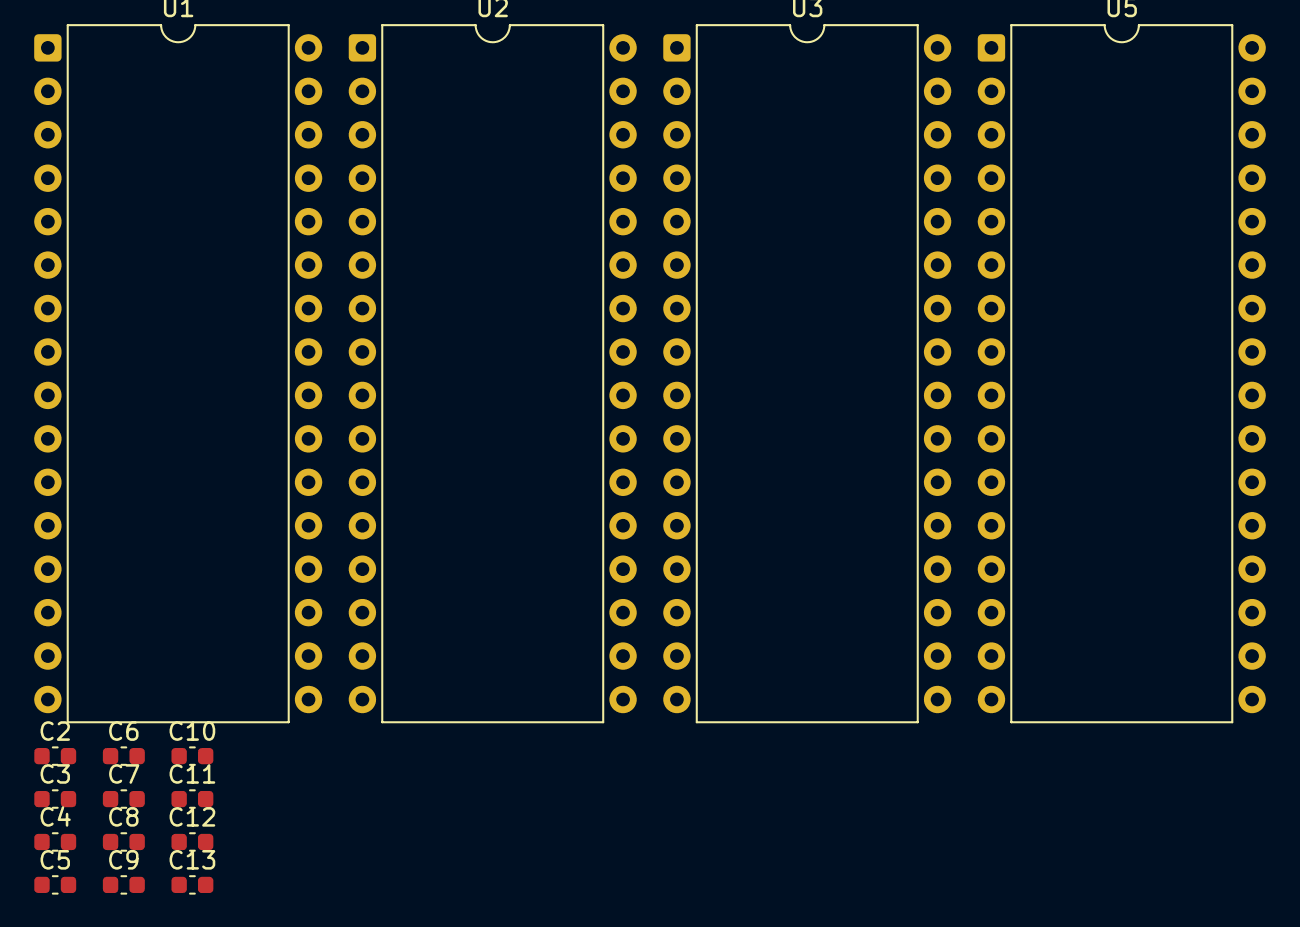
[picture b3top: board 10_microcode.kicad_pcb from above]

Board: 2 copper layers, 16 parts (0 on the bottom side), 11 nets, no tracks yet.

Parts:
C2, C3, C6, C7, C9, C10, C12, C13: 100nF; C_0603_1608Metric
C4, C5, C8, C11: 10nF; C_0603_1608Metric
U1, U2, U3, U5: AS6C4008-55PCN; DIP-32_W15.24mm

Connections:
/ir_opcode0: U1.12 (A0), U2.12 (A0), U3.12 (A0), U5.12 (A0)
/ir_opcode1: U1.11 (A1), U2.11 (A1), U3.11 (A1), U5.11 (A1)
/ir_opcode2: U1.10 (A2), U2.10 (A2), U3.10 (A2), U5.10 (A2)
/ir_opcode3: U1.9 (A3), U2.9 (A3), U3.9 (A3), U5.9 (A3)
/ir_opcode4: U1.8 (A4), U2.8 (A4), U3.8 (A4), U5.8 (A4)
/ir_opcode5: U1.7 (A5), U2.7 (A5), U3.7 (A5), U5.7 (A5)
/ir_opcode6: U1.6 (A6), U2.6 (A6), U3.6 (A6), U5.6 (A6)
/ir_opcode7: U1.5 (A7), U2.5 (A7), U3.5 (A7), U5.5 (A7)
/we: U1.29 (WE#), U2.29 (WE#), U3.29 (WE#), U5.29 (WE#)
GND: C2.2, C3.2, C4.2, C5.2, C6.2, C7.2, C8.2, C9.2, C10.2, C11.2, C12.2, C13.2, U1.1 (A18), U1.2 (A16), U1.3 (A14), U1.4 (A12), U1.16 (VSS), U1.22 (CE#), U1.23 (A10), U1.24 (OE#), U1.25 (A11), U1.26 (A9), U1.27 (A8), U1.28 (A13), U1.30 (A17), U1.31 (A15), U2.1 (A18), U2.2 (A16), U2.3 (A14), U2.4 (A12), U2.16 (VSS), U2.22 (CE#), U2.23 (A10), U2.24 (OE#), U2.25 (A11), U2.26 (A9), U2.27 (A8), U2.28 (A13), U2.30 (A17), U2.31 (A15), U3.1 (A18), U3.2 (A16), U3.3 (A14), U3.4 (A12), U3.16 (VSS), U3.22 (CE#), U3.23 (A10), U3.24 (OE#), U3.25 (A11), U3.26 (A9), U3.27 (A8), U3.28 (A13), U3.30 (A17), U3.31 (A15), U5.1 (A18), U5.2 (A16), U5.3 (A14), U5.4 (A12), U5.16 (VSS), U5.22 (CE#), U5.23 (A10), U5.24 (OE#), U5.25 (A11), U5.26 (A9), U5.27 (A8), U5.28 (A13), U5.30 (A17), U5.31 (A15)
VCC: C2.1, C3.1, C4.1, C5.1, C6.1, C7.1, C8.1, C9.1, C10.1, C11.1, C12.1, C13.1, U1.32 (VCC), U2.32 (VCC), U3.32 (VCC), U5.32 (VCC)
